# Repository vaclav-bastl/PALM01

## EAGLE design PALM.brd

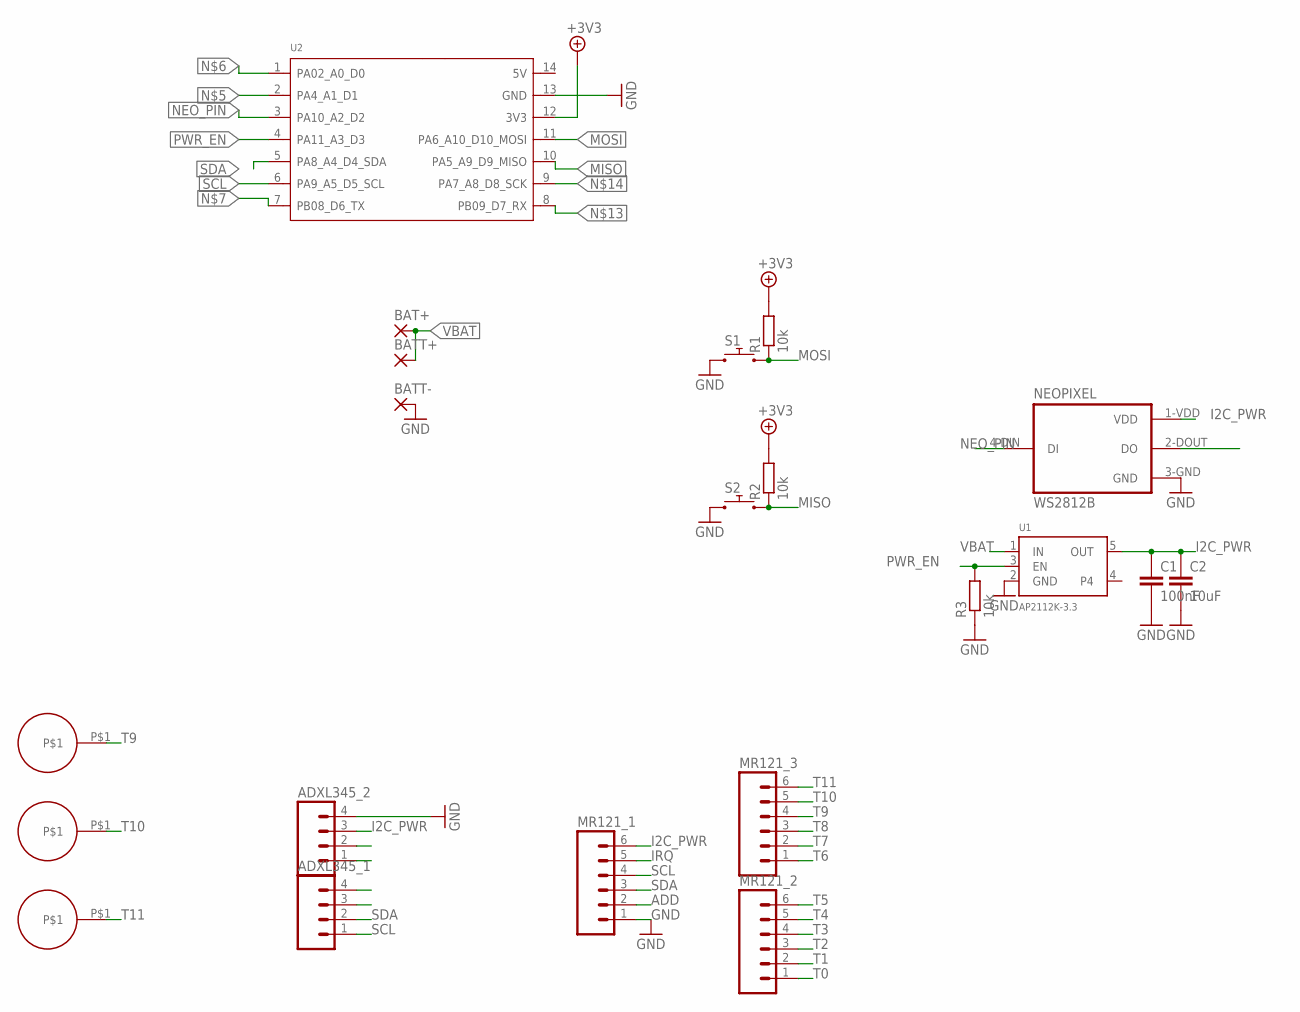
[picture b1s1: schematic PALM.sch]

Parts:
ADXL345_1, ADXL345_2: M04SMD_STRAIGHT_COMBO; 1X04_SMD_STRAIGHT_COMBO
BAT+: SMD2; SMD1,27-2,54
BATT+: SMD2; SMD1,27-2,54
BATT-: SMD2; SMD1,27-2,54
C1: 100nF; CAPACITOR0805
C2: 10uF; CAPACITOR0805
H2, H3, H4: FEROS_HEATHOLE; FEROS_HEATHOLE3.2
MR121_1, MR121_2, MR121_3: M06SMD-STRAIGHT-COMBO; 1X06_SMD_STRAIGHT_COMBO
NEOPIXEL: WS2812B
R1, R2, R3: 10k; 0805
S1, S2: PUSH_MOMENTARY_THT_6X6MM; TACTILE-PTH
U1: AP2112K-3.3; MICROBUILDER_SOT23-5
U2: MOUDLE-SEEEDUINO-XIAO-ESP32S3-SMD; MOUDLE14P-SMD-2.54-21X17.8MM

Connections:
+5V: R1.2, R2.2, U2.12 (3V3)
ADD: MR121_1.2
GND: ADXL345_2.4, BATT-.1, C1.2, C2.2, MR121_1.1, NEOPIXEL.3-GND (GND), R3.1, S1.1, S1.2 (1), S2.1, S2.2 (1), U1.2 (GND), U2.13 (GND)
I2C_PWR: ADXL345_2.3, C1.1, C2.1, MR121_1.6, NEOPIXEL.1-VDD (VDD), U1.5 (OUT)
IRQ: MR121_1.5
MISO: R2.1, S2.3 (2), S2.4 (2), U2.10 (PA5_A9_D9_MISO)
MOSI: R1.1, S1.3 (2), S1.4 (2), U2.11 (PA6_A10_D10_MOSI)
NEO_PIN: NEOPIXEL.4-DIN (DI), U2.3 (PA10_A2_D2)
PWR_EN: R3.2, U1.3 (EN), U2.4 (PA11_A3_D3)
SCL: ADXL345_1.1, MR121_1.4, U2.6 (PA9_A5_D5_SCL)
SDA: ADXL345_1.2, MR121_1.3, U2.5 (PA8_A4_D4_SDA)
T0: MR121_2.1
T1: MR121_2.2
T2: MR121_2.3
T3: MR121_2.4
T4: MR121_2.5
T5: MR121_2.6
T6: MR121_3.1
T7: MR121_3.2
T8: MR121_3.3
T9: H4.P$1, MR121_3.4
T10: H3.P$1, MR121_3.5
T11: H2.P$1, MR121_3.6
VBAT: BAT+.1, BATT+.1, U1.1 (IN)

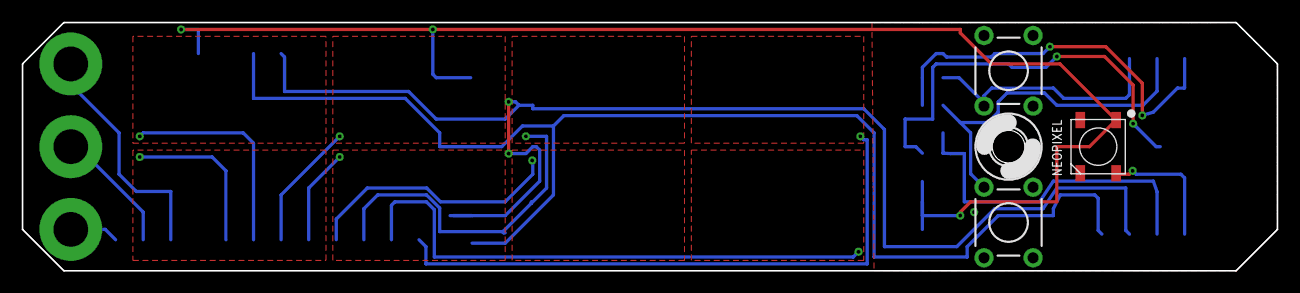
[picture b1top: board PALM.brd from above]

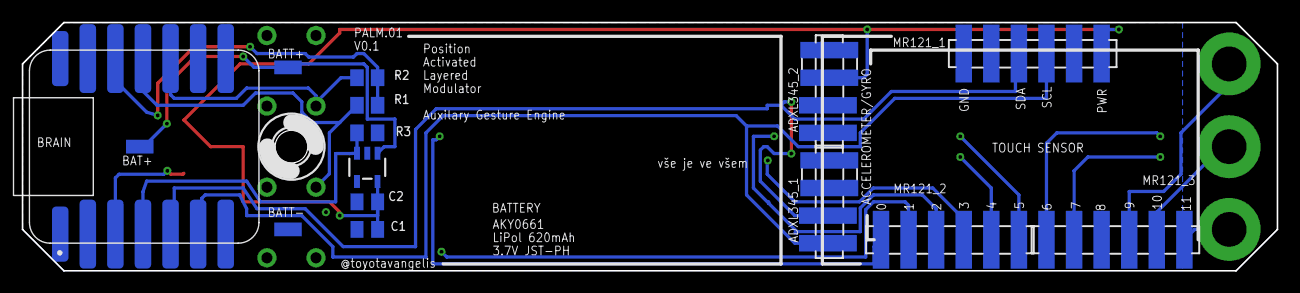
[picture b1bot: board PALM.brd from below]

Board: 2 copper layers, 115.6 x 22.9 mm, 22 parts (15 on the bottom side), 13 nets.

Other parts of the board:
H9: HOLE_3MM; 3MM_HOLE

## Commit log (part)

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2025-07-29 documentation
2025-07-29 added credits
2025-07-31 fixed autoconfig and new calibration. added gerbers and slicer date
2025-09-16 added midi input parsing to the multi midi - tested it only on BLE so far
2025-10-11 better accelerometer filtering, no more out of range CC, preset cleanup, smarter preset switching, each finger priority is handeled based on leftHand=true
2025-10-11 added preset rotations and tried to do captive wifi (and failed)
2025-10-11 minor default preset changes
2025-10-12 global preset rotations work now
2025-10-12 added note sending preset mode - chord mode
2025-10-18 note mode: first pressed note is the root note. LITTLE B is CC selector (see manual)
2025-10-18 lowered latency
2025-10-18 midi channel for note mode set in the preset mode + allnotes off when leaving not mode
2025-10-25 added 7th chords. C+B = C7, C+D=D7 etc.
2025-10-26 added instructions for 3d printing svg for the overlay
2025-10-26 gui mockup
2025-10-26 added working captive portal with semi working gui password is palm1234
2025-10-26 lower wifi power for lower heat emition. will probably drop more once running from 3V3 battery instead of 5V usb
2025-10-26 added gui mockup
2025-10-26 figuring out the html
2025-10-26 working captive interaction on the image
2025-11-09 added velocity to the first touched note in note mode. also fixed non-reseting CC
2025-11-09 reset touch CCs when entering note mode + clip the touch velocity
